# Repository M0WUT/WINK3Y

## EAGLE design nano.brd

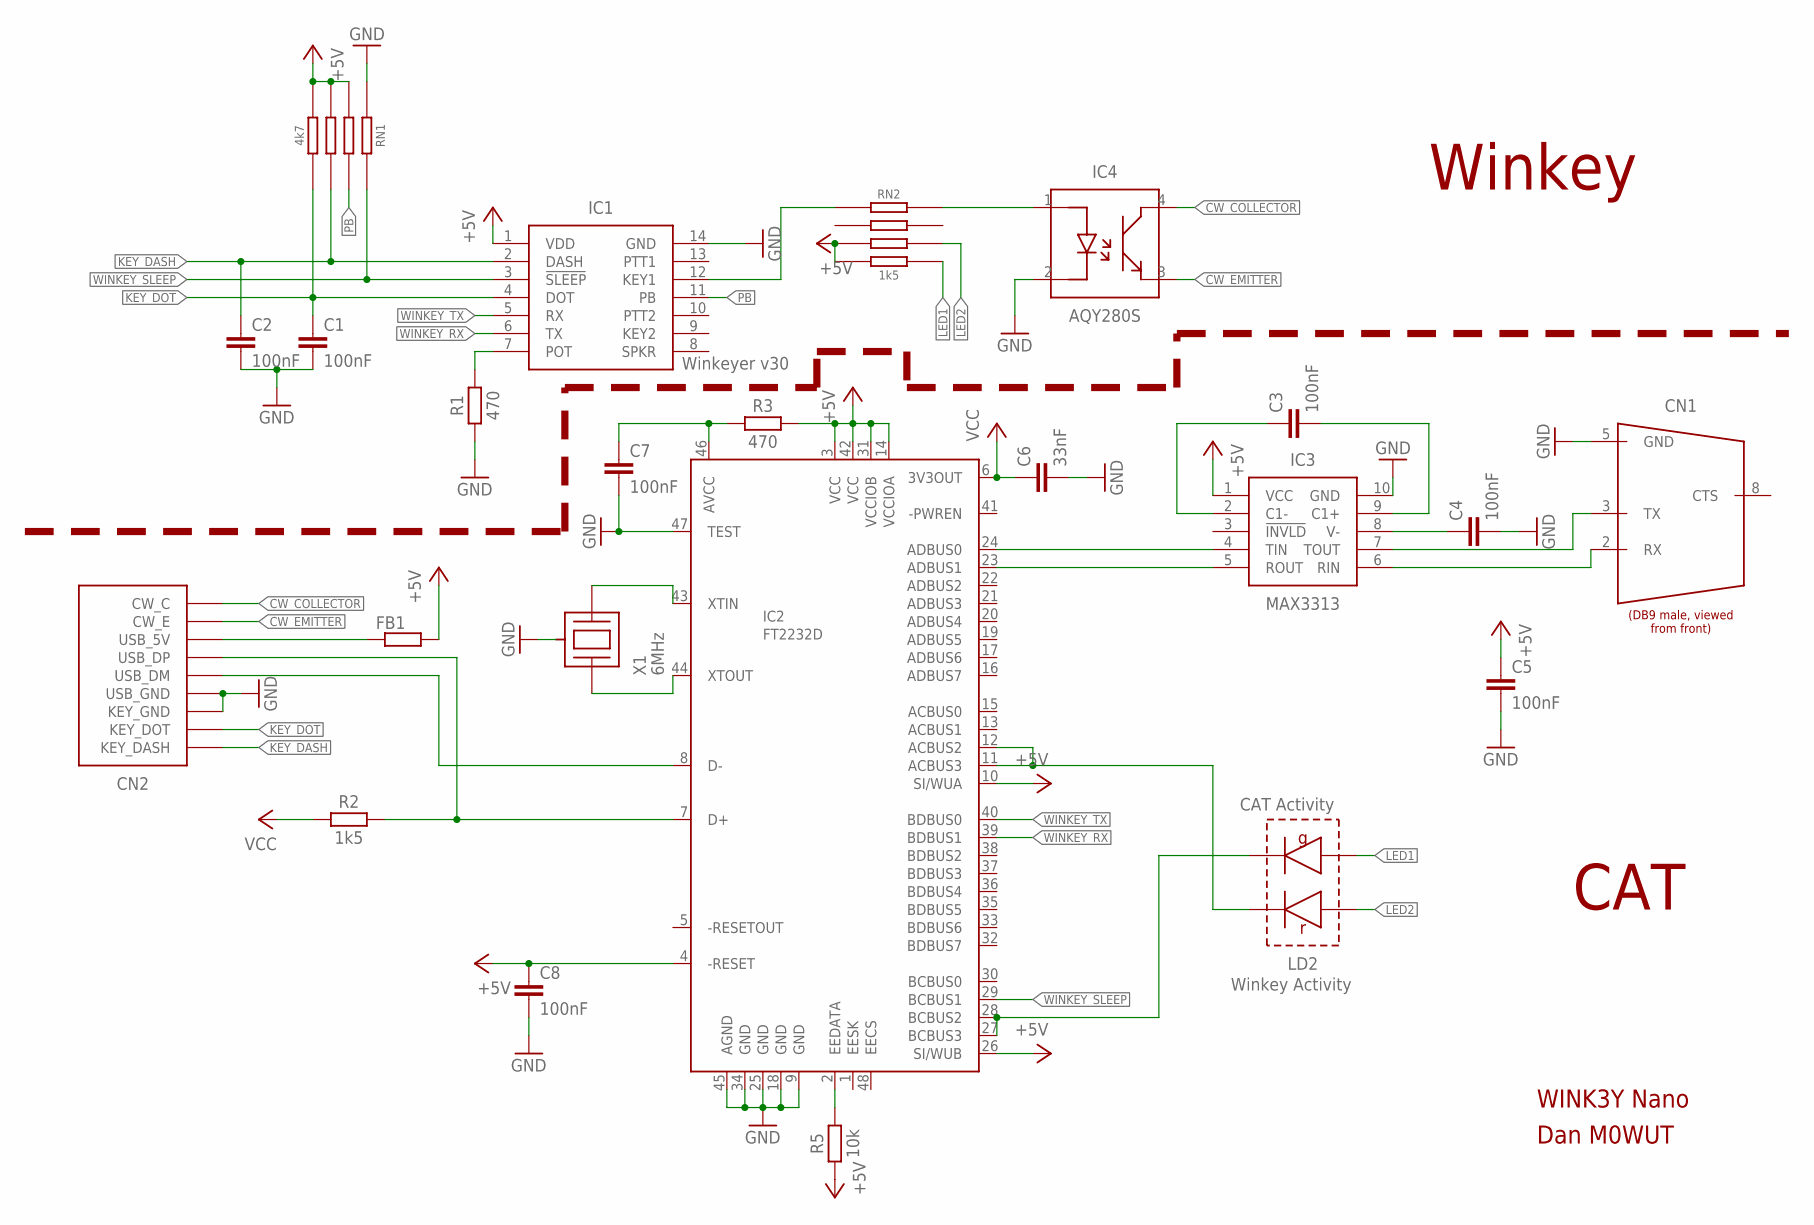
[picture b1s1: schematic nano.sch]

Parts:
C1, C2, C3, C4, C5, C7, C8: 100nF; C0402
C6: 33nF; C0402
CN1: CONN_DB9_MALE; CONN_DB9
CN2: CONN_WINK3Y; CONN_2MMX9
FB1: R-EU_R0805; R0805
IC1: WINKEYER; SO14
IC2: FT2232D; QFP48-7X7
IC3: IC_MAX3313; IC_UMAX10
IC4: IC_AQY280S
LD2: LED_KINGBRIGHT_KPTB
R1, R3: 470; R0402
R2: 1k5; R0402
R5: 10k; R0402
RN1: 4k7; R_BOURNS_CAY16-J4
RN2: 1k5; R_BOURNS_CAY16-J4
X1: 6MHz; XTAL_MURATA_3-PIN-RES

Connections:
+5V: C5.1, C8.1, FB1.2, IC1.1 (VDD), IC2.3 (VCC), IC2.4 (-RESET), IC2.10 (SI/WUA), IC2.14 (VCCIOA), IC2.26 (SI/WUB), IC2.31 (VCCIOB), IC2.42 (VCC), IC3.1 (VCC), R3.2, R5.1, RN1.2, RN1.3, RN1.4, RN2.3, RN2.4
CAT_RX: IC2.23 (ADBUS1), IC3.5 (ROUT)
CAT_TX: IC2.24 (ADBUS0), IC3.4 (TIN)
CW_COLLECTOR: CN2.CW_COLLECTOR (CW_C), IC4.4 (COLLECTOR)
CW_EMITTER: CN2.CW_EMITTER (CW_E), IC4.3 (EMITTER)
GND: C1.2, C2.2, C4.2, C5.2, C6.2, C7.2, C8.2, CN1.5 (GND), CN2.KEY_GND, CN2.USB_GND, IC1.14 (GND), IC2.9 (GND), IC2.18 (GND), IC2.25 (GND), IC2.34 (GND), IC2.45 (AGND), IC2.47 (TEST), IC3.10 (GND), IC4.2 (CATHODE), R1.1, RN1.1, X1.GND (CAN)
KEY_DASH: C2.1, CN2.KEY_DASH, IC1.2 (DASH), RN1.3A
KEY_DOT: C1.1, CN2.KEY_DOT, IC1.4 (DOT), RN1.4A
LED1: LD2.3 (G_ANODE), RN2.4A
LED2: LD2.1 (R_ANODE), RN2.3A
unnamed: C7.1, IC2.46 (AVCC), R3.1
unnamed: CN2.USB_5V, FB1.1
unnamed: IC2.43 (XTIN), X1.2 (XTAL2)
unnamed: CN1.3 (TX), IC3.7 (TOUT)
unnamed: CN1.2 (RX), IC3.6 (RIN)
unnamed: C3.1, IC3.2 (C1-)
unnamed: C3.2, IC3.9 (C1+)
unnamed: C4.1, IC3.8 (V-)
unnamed: IC2.44 (XTOUT), X1.1 (XTAL1)
unnamed: CN2.USB_DM, IC2.8 (D-)
unnamed: IC1.12 (KEY1), RN2.1
unnamed: IC4.1 (ANODE), RN2.1A
unnamed: IC1.7 (POT), R1.2
unnamed: IC2.11 (ACBUS3), IC2.12 (ACBUS2), LD2.2 (R_CATHODE)
unnamed: IC2.2 (EEDATA), R5.2
unnamed: CN2.USB_DP, IC2.7 (D+), R2.2
PB: IC1.11 (PB), RN1.2A
VCC: C6.1, IC2.6 (3V3OUT), R2.1
WINKEY_ACT: IC2.27 (BCBUS3), IC2.28 (BCBUS2), LD2.4 (G_CATHODE)
WINKEY_RX: IC1.6 (TX), IC2.39 (BDBUS1)
WINKEY_SLEEP: IC1.3 (!SLEEP), IC2.29 (BCBUS1), RN1.1A
WINKEY_TX: IC1.5 (RX), IC2.40 (BDBUS0)

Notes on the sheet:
Winkey
CAT
WINK3Y Nano
Dan M0WUT
Winkeyer v30
CAT Activity
Winkey Activity

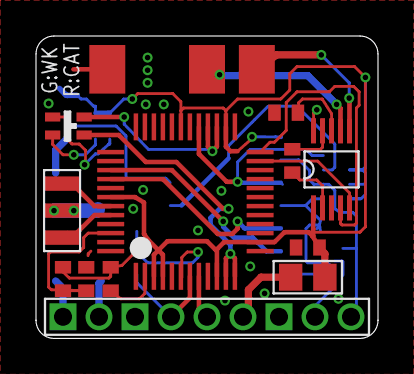
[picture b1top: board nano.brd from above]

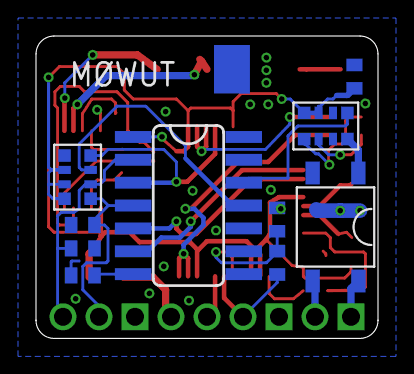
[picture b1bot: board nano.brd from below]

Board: 2 copper layers, 19.0 x 16.8 mm, 23 parts (10 on the bottom side), 32 nets.

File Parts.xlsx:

Qty | Value | Parts | Farnell Number | Unit cost (GBP exc VAT) | Total (GBP inc VAT)
1.0 | PCB |  |  |  | 1.5
1.0 |  | FB1 | RS: 724-1532 | 0.05 | 0.06
7.0 | 100nF | C1, C2, C3, C4, C5, C7, C8 | 2810260.0 | 0.014 | 0.1176
1.0 | 10k | R5 | 2059239.0 | 0.016 | 0.0192
1.0 | 1k5 | R2 | 2072645.0 | 0.008 | 0.0096
1.0 | 1k5 | RN2 | 2333509.0 | 0.068 | 0.0816
1.0 | 33nF | C6 | 1865445.0 | 0.054 | 0.0648
2.0 | 470R | R1, R3 | 2447178.0 | 0.004 | 0.0096
1.0 | 4k7 | RN1 | 1770136.0 | 0.061 | 0.0732
1.0 | 6MHz | X1 | 1170434.0 | 0.284 | 0.3408
1.0 | CONN_DB9_MALE | CN1 | 698064.0 | 0.332 | 0.3984
1.0 | D SUB BACKSHELL | N/A | 2346835.0 | 0.714 | 0.8568
1.0 | FT2232D | IC2 | 1615843.0 | 5.26 | 6.312
1.0 | IC_AQY280S | IC4 | RS: 811-3296 | 1.42 | 1.704
1.0 | IC_MAX3313 | IC3 | 2511704.0 | 1.4 | 1.68
1.0 | LED_KINGBRIGHT_KPTB | LD2 | 2426236.0 | 0.098 | 0.1176
1.0 | WINKEYER | IC1 | N/A | ~10USD
368 |  |  |  | TOTAL: | 13.3452 | (plus Winkeyer)

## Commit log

2018-10-30 upload of v1 release
